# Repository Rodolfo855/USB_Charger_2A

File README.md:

# USB_Charger_2A
Switching Lithium Battery Charger ( 2 Amps )

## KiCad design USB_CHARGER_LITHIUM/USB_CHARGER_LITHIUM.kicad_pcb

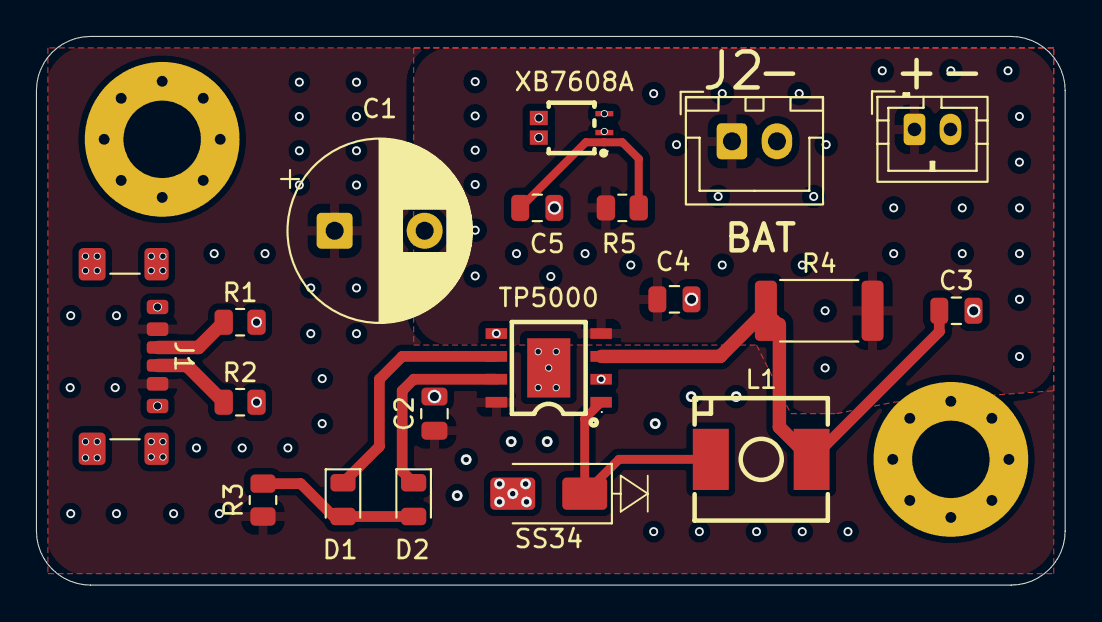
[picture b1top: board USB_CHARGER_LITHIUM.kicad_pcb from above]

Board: 2 copper layers, 57.2 x 30.5 mm, 21 parts (0 on the bottom side), 12 nets.

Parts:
C1: 47uF-16V; CP_Radial_D10.0mm_P5.00mm
C2: 1uF-0805; C_0805_2012Metric
C3, C4: 10uF-0805; C_0805_2012Metric
C5: 100nF-0805; C_0805_2012Metric
D1, D2: LED; LED_0805_2012Metric
H1, H2: MountingHole; MountingHole_4.3mm_M4_Pad_Via
J1: USB4135; USB_C_Receptacle_GCT_USB4135-GF-A_6P_TopMnt_Horizontal
J2: Conn_01x02; JST_XH_B2B-XH-A_1x02_P2.50mm_Vertical
J3: Conn_01x02; JST_PH_B2B-PH-K_1x02_P2.00mm_Vertical
L1: 4.7uH; C76857_IND-SMD_L7_1-W6_5
R1, R2: 5.1K-1%; R_0805_2012Metric
R3, R5: 1k-0805; R_0805_2012Metric
R4: 0.05R 3W; R_2512_6332Metric
SS34: SS34; D_SMA
TP5000: TP5000X-4.2-ESOP8; C5447152_ESOP-8_L4_9-W3_9-P1_27-LS6_0-BL-EP
XB7608A: XB7608A; C669688_CPC-5_L2_6-W2_6-LS4_2_XB7608A

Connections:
+BATT: C4.1, J2.1, J3.1, R4.2, R5.1, TP5000.4 (BAT)
GND: C1.2, C2.2, C3.2, C4.2, C5.2, J1.A12 (GND), J1.B12 (GND), J1.S1 (SHIELD), J3.2, R1.2, R2.2, SS34.2 (A), TP5000.2 (GND), TP5000.5 (TS), XB7608A.4 (VM), XB7608A.5 (VM)
GNDPWR: J2.2, XB7608A.2 (GND), XB7608A.3 (GND)
unnamed: D1.2 (A), D2.2 (A), R3.2
unnamed: D1.1 (K), TP5000.6 (*STDBY)
unnamed: D2.1 (K), TP5000.7 (*CHRG)
unnamed: L1.1, SS34.1 (K), TP5000.1 (LX)
unnamed: J1.A5 (CC1), R1.1
unnamed: J1.B5 (CC2), R2.1
unnamed: C3.1, L1.2, R4.1, TP5000.3 (VS)
unnamed: C5.1, R5.2, XB7608A.1 (VDD)
VBUS: C1.1, C2.1, J1.A9 (VBUS), J1.B9 (VBUS), R3.1, TP5000.8 (VIN)

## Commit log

2026-06-10 USB setup
2026-06-11 Added battery chip regulator footprint/3d model
2026-06-11 Working on wiring IC
2026-06-12 Need to include battery management ic
2026-06-12 Finished Schematic
2026-06-12 Added symbol for battery management ic
2026-06-13 Added libraries and assigned footprints
2026-06-13 Placed components in pcb
2026-06-14 Fixed shchematic grid and added ground copper planes
2026-06-14 Finished pcb design. Working on BOM and Positions
2026-06-14 Gerber files, BOM, and positions files added
2026-06-16 Fixed gerber files and BOM/Positions
2026-06-24 Increased vias radius, and smoothed out corners
2026-06-24 Added pdf and gerber 1.1 files
2026-06-30 Rev 1.1
2026-06-30 Gerbed files 1.1
